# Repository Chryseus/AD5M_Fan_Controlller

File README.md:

# AD5M Fan Controlller

This is a work in progress fan controller for the Flashforge AD5M / AD5X 3d printer that provides remote fan control over Wifi as well as chamber monitoring.

## Hardware

This is designed for the ESP32 C3 Super Mini but will work with any arduino compatible device that supports Wifi.

BME280 is used for temperature, pressure and humidity sensing.

ENS160 is used for air quality sensing.

Any PWM driver will work for the fans, I've used DRV8871.

Recirculation fan is a 5015 blower, 24V 8500 RPM max.

Exhaust fan is a 4020 24V.

Power is drawn from the built in 24V supply and regulated down to 5V for the ESP32 using a LMR14006Y buck converter (you could use a 7805 instead), the ESP32 3.3V regulator is used to power the sensors.

## 3D Printed Parts

For the recirculation duct [this](https://www.printables.com/model/1243577-flashforge-adventurer-5m-recirculating-air-duct-50) is used for the AD5M, for AD5X users [this](https://www.printables.com/model/1473971-ad5x-internal-circulation-air-filtration-duct-with) or [this](https://www.printables.com/model/1472826-ad5x-recirculation-duct-blower-5015) may work.

For the exhaust duct I have used [this](https://www.printables.com/model/1375541-adventurer-5m-venting-kit-for-the-non-pro-version).

### Roadmap

- [x] Manual fan control

- [x] Sensor display

- [x] Schematic

- [ ] 3D printed mounting parts

- [ ] Automatic mode based on sensor data

**Possible future additions**

- [ ] Data logging / plotting

- [ ] Send data to external server

- [ ] 3D printer communication

- [x] Custom PCB

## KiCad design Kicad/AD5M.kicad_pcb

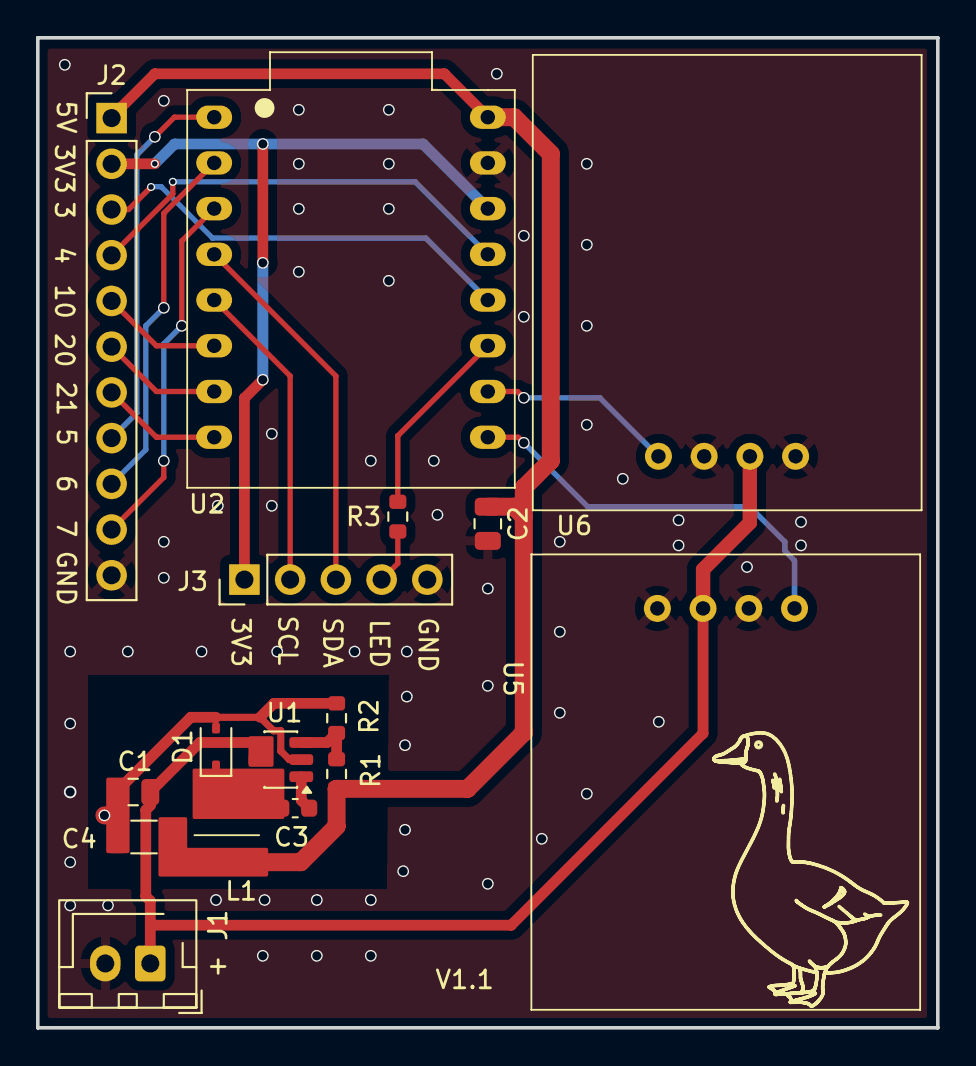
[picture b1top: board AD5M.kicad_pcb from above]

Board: 2 copper layers, 50.0 x 55.0 mm, 16 parts (0 on the bottom side), 21 nets.

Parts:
C1, C2: 1u; C_0805_2012Metric
C3: 100n; C_0603_1608Metric
C4: 22u; C_1206_3216Metric
D1: 1N5819HW; D_SOD-323
J1: Vin; JST_XH_B2B-XH-AM_1x02_P2.50mm_Vertical
J2: Conn_01x11; PinHeader_1x11_P2.54mm_Vertical
J3: Ext; PinHeader_1x05_P2.54mm_Vertical
L1: 6.8u; SMNR4030
R1: 54.9k; R_0603_1608Metric
R2: 10k; R_0603_1608Metric
R3: 1k; R_0603_1608Metric
U1: LMR14006Y; TSOT-23-6
U2: ESP32 C3 SuperMini; ESP32_SuperMini_C3
U5, U6: DRV8871 Module

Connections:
3: J2.3, U2.12 (3_A3)
3.3V: J2.2, J3.1, U2.14 (3.3V)
4: J2.4, U2.13 (4_A4_SCK)
5: J2.8, U2.1 (5_A5_MISO)
5V: C2.1, C4.1, J2.1, L1.2, R1.1, U2.16 (5V)
6: J2.9, U2.2 (6_MOSI)
7: J2.10, U2.3 (7_SS)
10: J2.5, U2.6 (10)
20: J2.6, U2.7 (20_RX)
21: J2.7, U2.8 (21_TX)
24V: C1.1, J1.1, U1.4 (~SHDN), U1.5 (Vin), U5.3 (Vm), U6.3 (Vm)
FAN_EXHAUST: U2.10 (1_A1), U6.1 (In_2)
FAN_RECIRC: U2.9 (0_A0), U5.1 (In_2)
GND: C1.2, C2.2, C4.2, D1.2 (A), J1.2, J2.11, J3.5, R2.2, U1.2 (GND), U2.15 (GND), U5.2 (In_1), U5.4 (GND), U6.2 (In_1), U6.4 (GND)
unnamed: C3.2, D1.1 (K), L1.1, U1.6 (SW)
unnamed: J3.4, R3.1
unnamed: C3.1, U1.1 (CB)
unnamed: R1.2, R2.1, U1.3 (FB)
SCL: J3.2, U2.5 (9_SCL)
SDA: J3.3, U2.4 (8_SDA)
TVOC_LED: R3.2, U2.11 (2_A2)

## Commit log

2026-02-12 Initial version
2026-02-12 Made sensors optional Added support for BMP280 Added github link to interface
2026-02-13 Added schematic.
2026-02-16 Fixed exhaust fan output Increased PWM frequency to 30kHz Added logic to ensure fan startup Added TVOC High LED support Updated schematic
2026-02-28 Code tidy Add Wifi connection checking
2026-02-28 Update Schematic, Add PCB gerbers.
2026-02-28 Add KiCad files.
2026-03-09 Fixed ESP32 footprint & symbol Updated KiCad files Updated gerbers to board version 1.1
2026-03-09 Update schematic
